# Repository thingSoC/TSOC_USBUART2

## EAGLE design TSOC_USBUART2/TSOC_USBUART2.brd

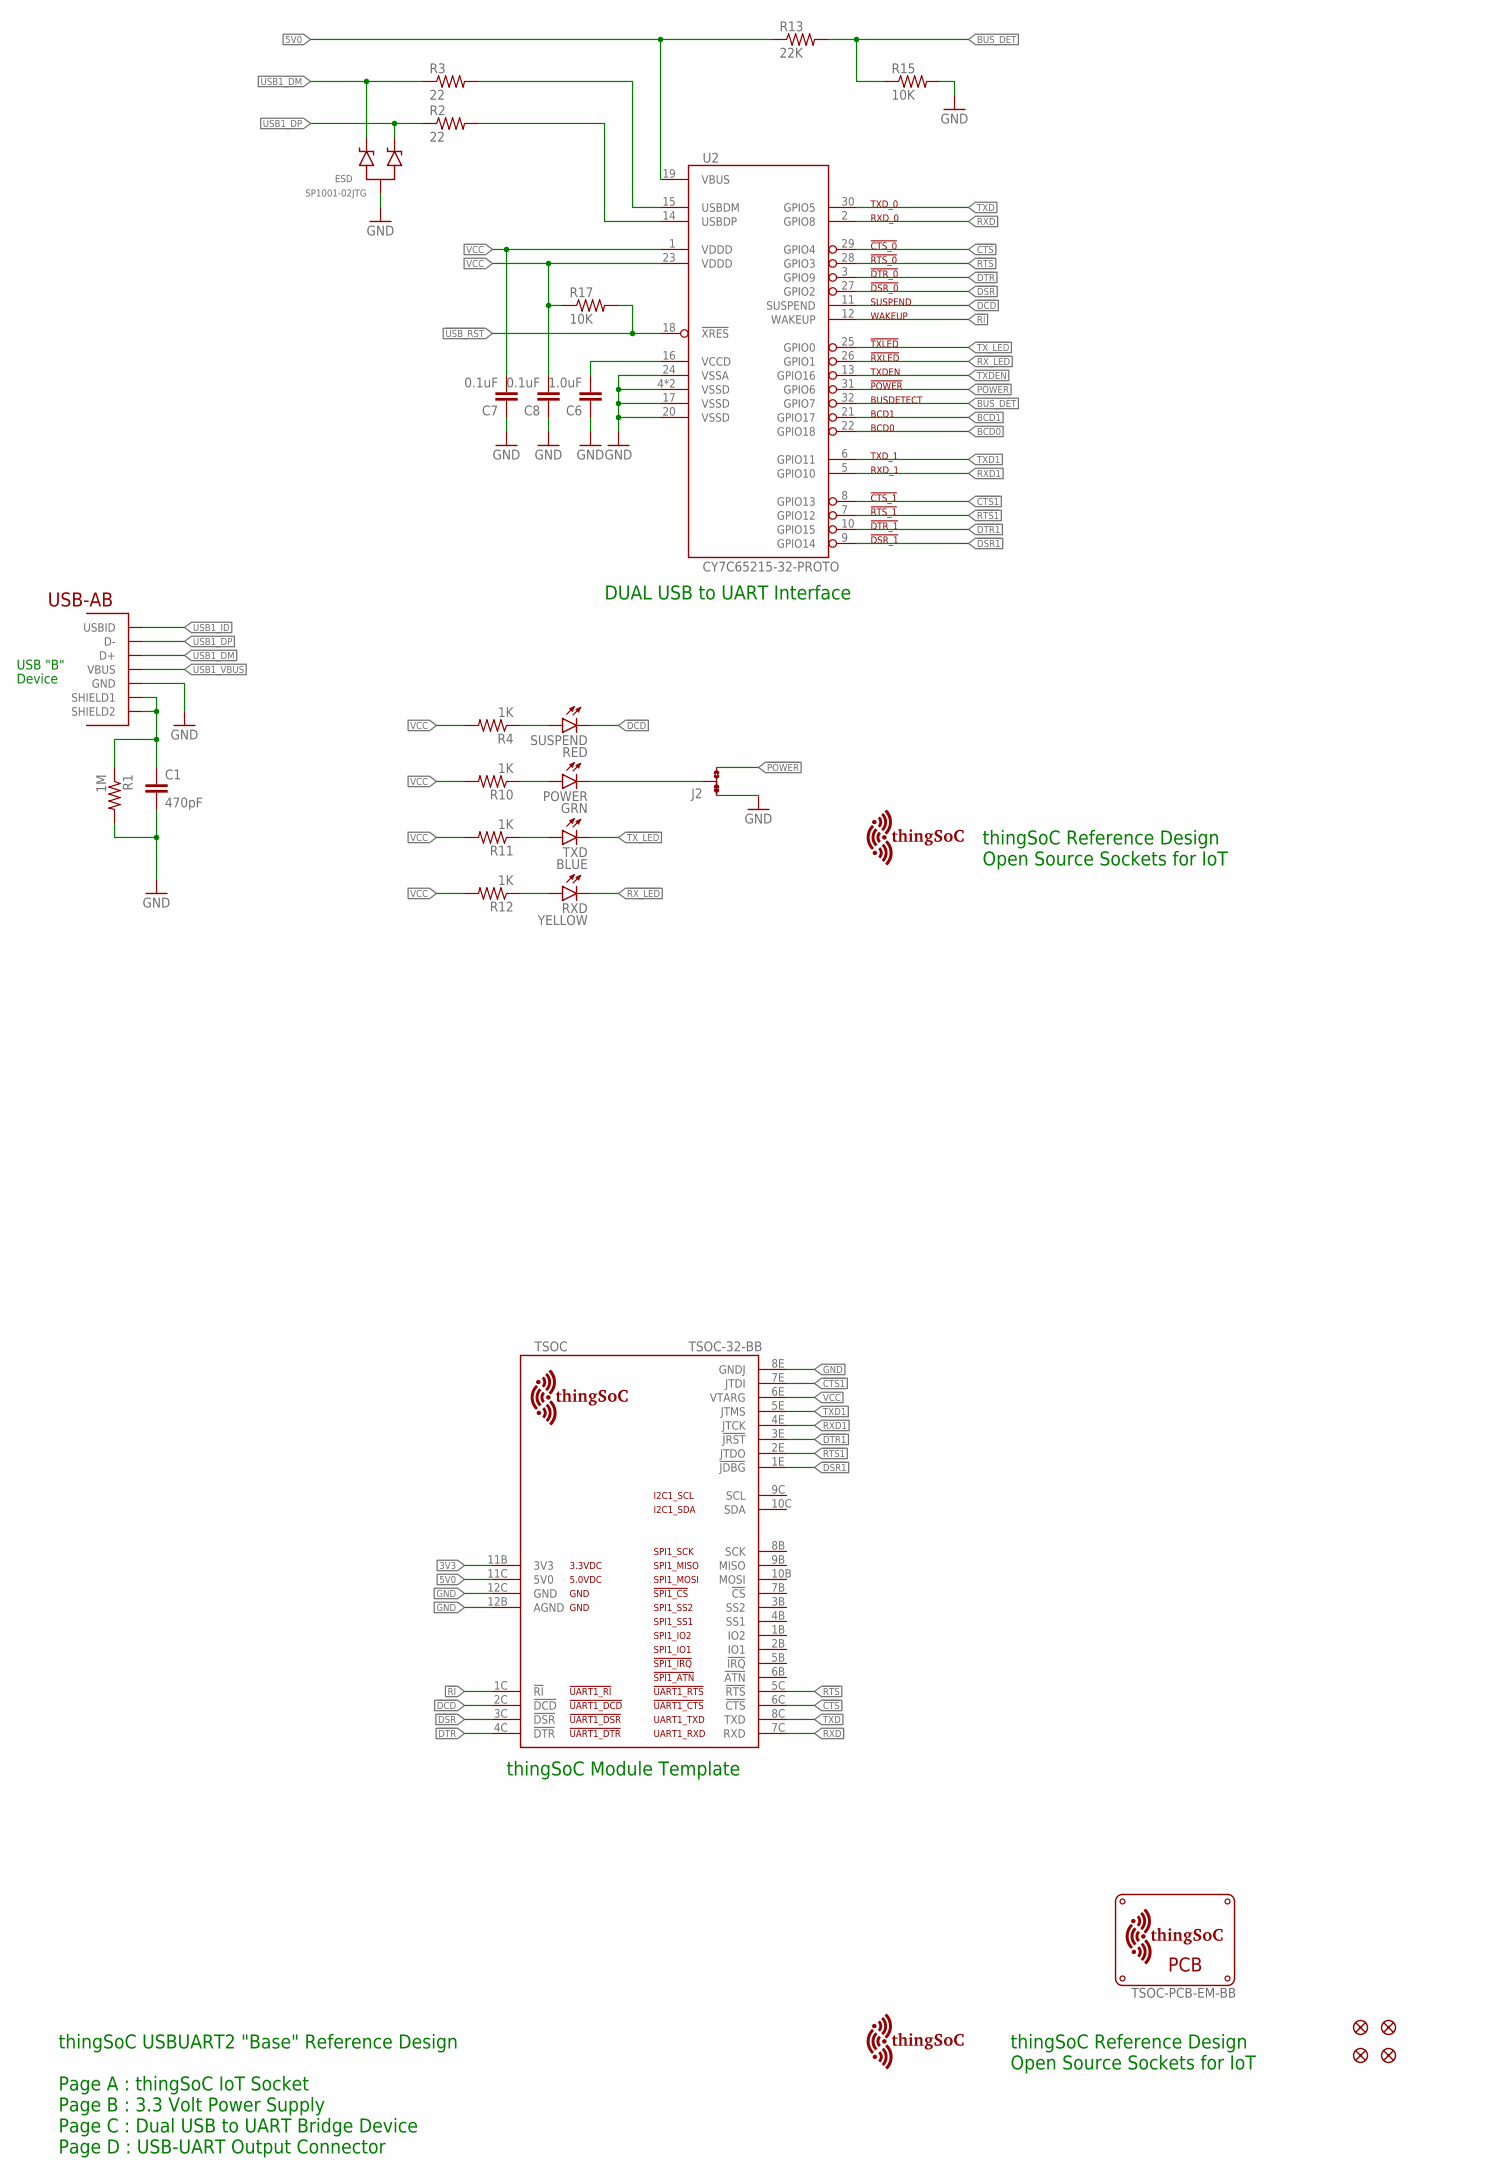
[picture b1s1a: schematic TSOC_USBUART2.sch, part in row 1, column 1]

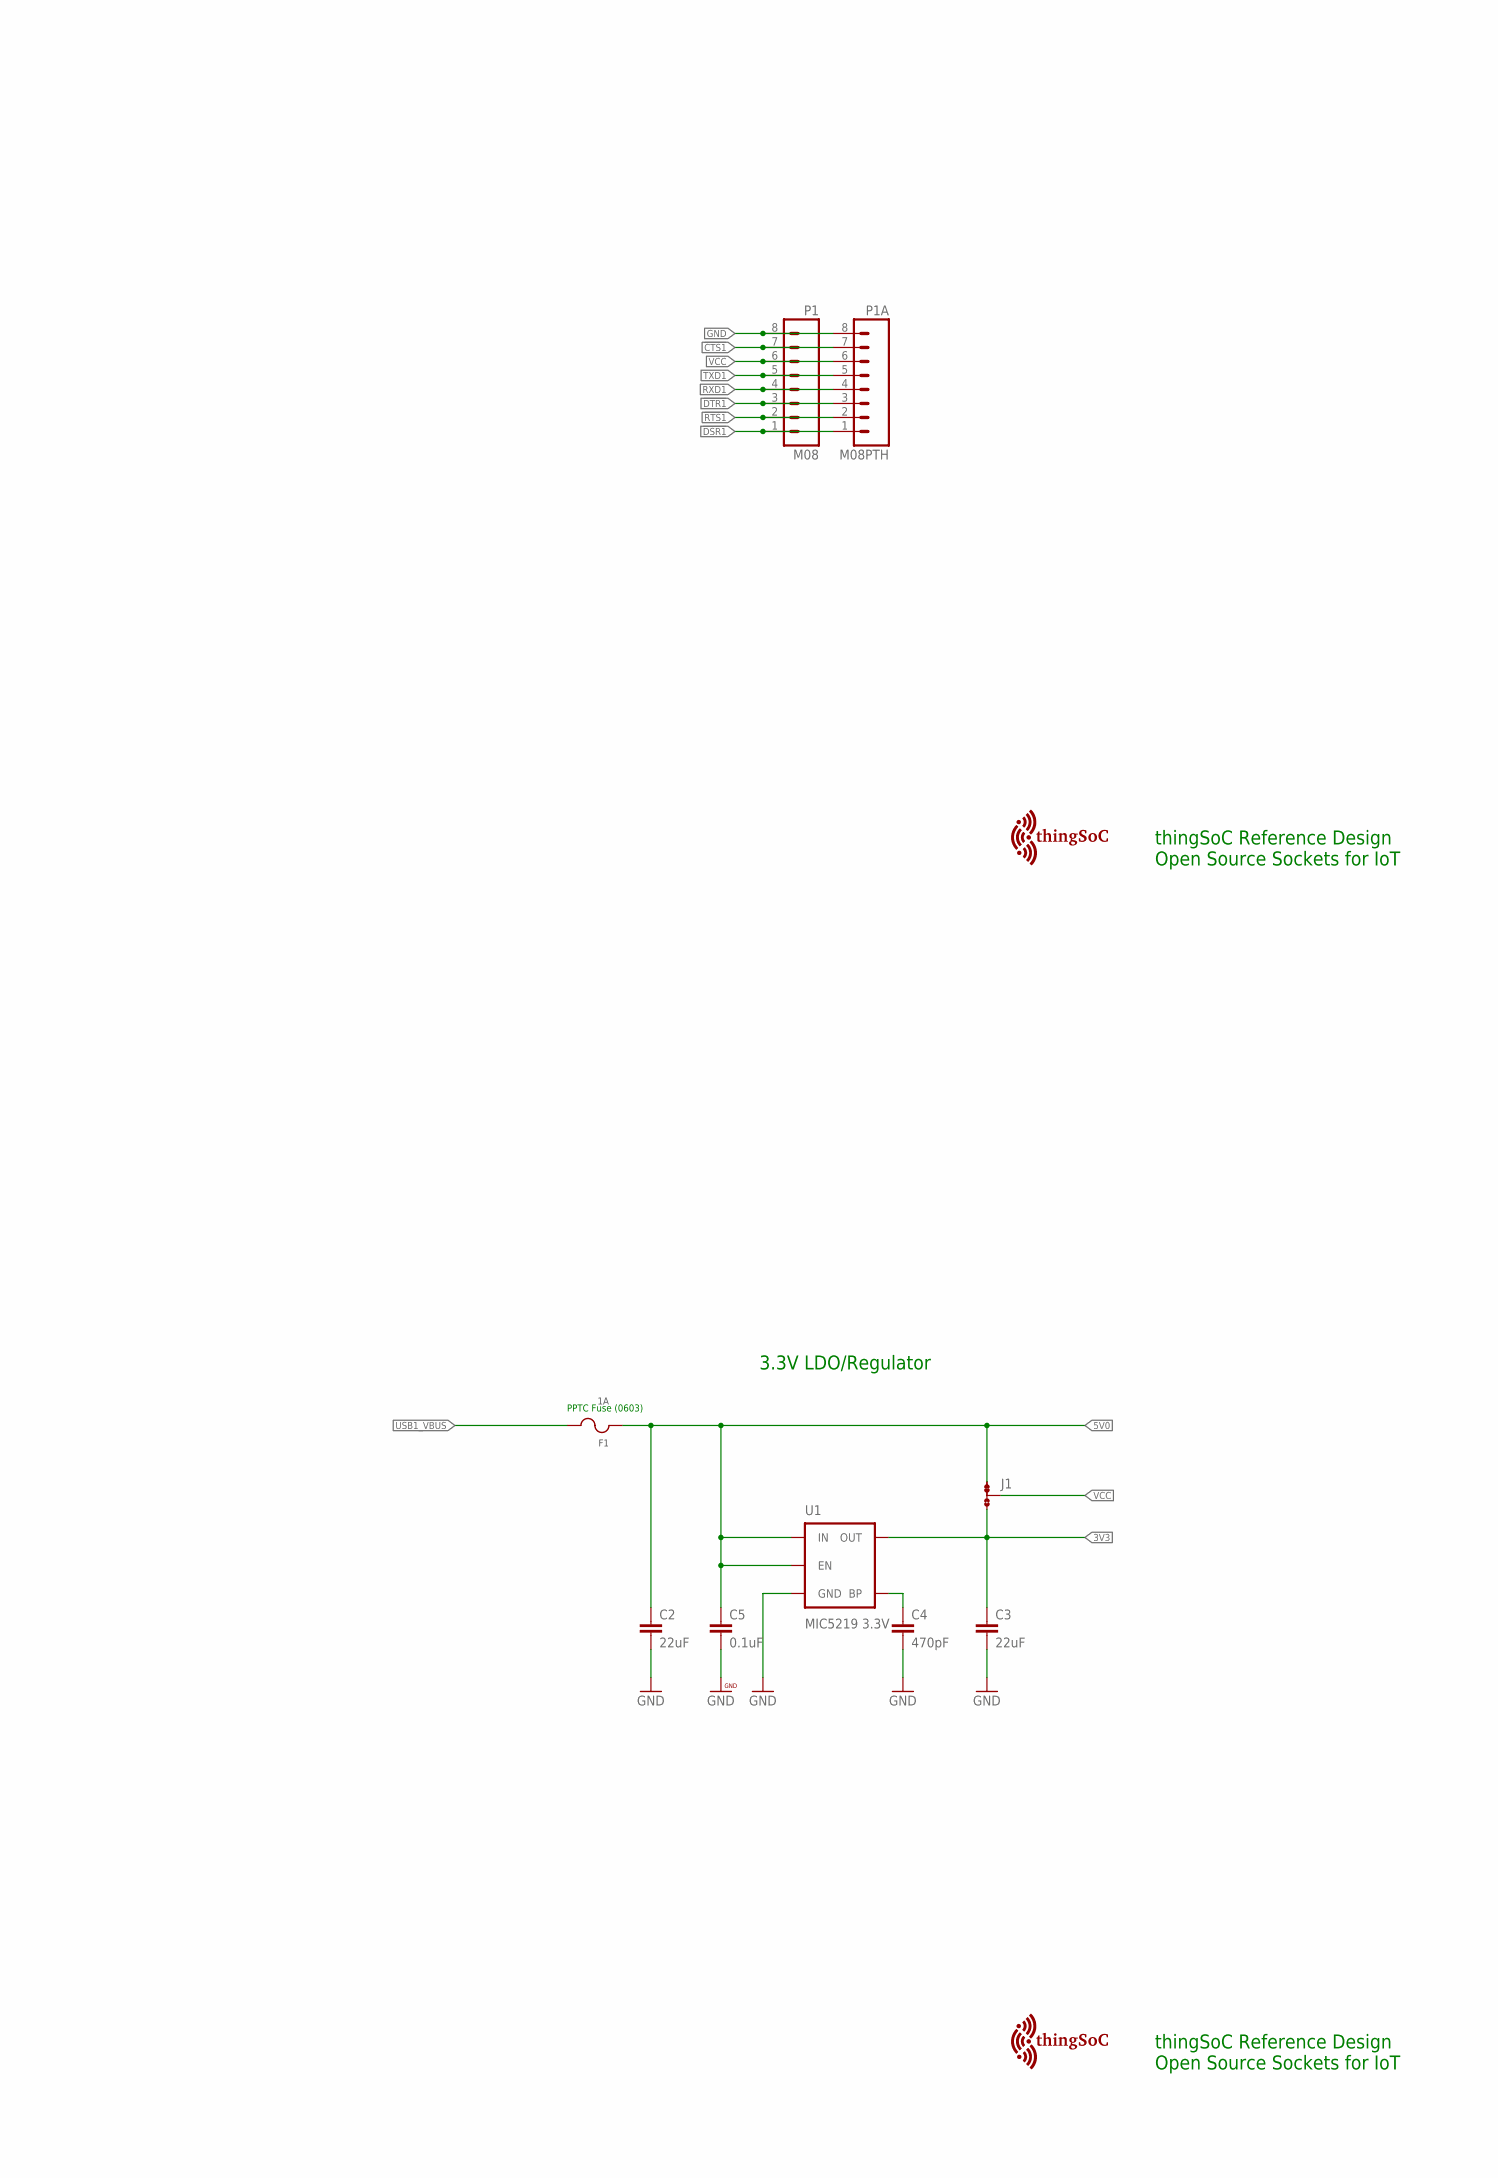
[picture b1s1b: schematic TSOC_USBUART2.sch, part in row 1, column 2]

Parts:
C1, C4: 470pF; EIA-0603
C2, C3: 22uF; EIA-1206
C5, C7, C8: 0.1uF; EIA-0603
C6: 1.0uF; EIA-0603
ESD: SP1001-02JTG; SC70-3
F1: 1A; EIA-0603
FID1, FID2, FID3, FID4: FIDUCIALUFIDUCIAL; MICRO-FIDUCIAL
J1, J2: JMP-3-1_2
P1: M08; 1X08-SMD-FEMALE
P1A: M08PTH; 1X08
POWER: GRN; LED-0603
R1: 1M; EIA-0603
R2, R3: 22; EIA-0603
R4, R10, R11, R12: 1K; EIA-0603
R13: 22K; EIA-0603
R15, R17: 10K; EIA-0603
RXD: YELLOW; LED-0603
SUSPEND: RED; LED-0603
TSOC: TSOC-32-BB; TSOC-BB-S32
TXD: BLUE; LED-0603
U1: MIC5219 3.3V; SOT23-5
U2: CY7C65215-32-PROTO; QFN32-PROTO
U$1: TSOC-PCB-EM-BB; TSOC-EM-BB
U$3: TSOC-LOGO-LRG
U$4, U$5, U$6: TSOC-LOGO; TSOC-LOGO-BLANK
USB: USB_AB; USB-AB-MICRO-SMD

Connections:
3V3: C3.1, J1.3, TSOC.11B (3V3), U1.5 (OUT)
5V0: C2.1, C5.1, F1.1, J1.1, R13.1, TSOC.11C (5V0), U1.1 (IN), U1.3 (EN), U2.19 (VBUS)
!CTS: TSOC.6C (!CTS), U2.29 (GPIO4)
!CTS1: P1.7, P1A.7, TSOC.7E (JTDI), U2.8 (GPIO13)
!DCD: SUSPEND.C, TSOC.2C (!DCD), U2.11 (SUSPEND)
!DSR: TSOC.3C (!DSR), U2.27 (GPIO2)
!DSR1: P1.1, P1A.1, TSOC.1E (!JDBG), U2.9 (GPIO14)
!DTR: TSOC.4C (!DTR), U2.3 (GPIO9)
!DTR1: P1.3, P1A.3, TSOC.3E (!JRST), U2.10 (GPIO15)
!POWER: J2.3, U2.31 (GPIO6)
!RI: TSOC.1C (!RI), U2.12 (WAKEUP)
!RTS: TSOC.5C (!RTS), U2.28 (GPIO3)
!RTS1: P1.2, P1A.2, TSOC.2E (JTDO), U2.7 (GPIO12)
!RX_LED: RXD.C, U2.26 (GPIO1)
!TX_LED: TXD.C, U2.25 (GPIO0)
!USB_RST: R17.2, U2.18 (!XRES)
BCD0: U2.22 (GPIO18)
BCD1: U2.21 (GPIO17)
BLU: R11.1, TXD.A
BUS_DET: R13.2, R15.1, U2.32 (GPIO7)
BYPASS1: C4.1, U1.4 (BP)
GND: C1.2, C2.2, C3.2, C4.2, C5.2, C6.1, C7.1, C8.1, ESD.3 (A), J2.1, P1.8, P1A.8, R1.2, R15.2, TSOC.8E (GNDJ), TSOC.12B (AGND), TSOC.12C (GND), U1.2 (GND), U2.4 (VSSD), U2.17 (VSSD), U2.20 (VSSD), U2.24 (VSSA), U2.EXP (VSSD), USB.GND
GRN: POWER.A, R10.1
PWR: J2.2, POWER.C
RED: R4.1, SUSPEND.A
RXD: TSOC.7C (RXD), U2.2 (GPIO8)
RXD1: P1.4, P1A.4, TSOC.4E (JTCK), U2.5 (GPIO10)
TXD: TSOC.8C (TXD), U2.30 (GPIO5)
TXD1: P1.5, P1A.5, TSOC.5E (JTMS), U2.6 (GPIO11)
TXDEN: U2.13 (GPIO16)
USB1_ID: USB.ID (USBID)
USB1_M: R3.2, U2.15 (USBDM)
USB1_P: R2.2, U2.14 (USBDP)
USB1_SHIELD: C1.1, R1.1, USB.SHIELD1, USB.SHIELD2
USB1_VBUS: F1.2, USB.VBUS
VCC: C7.2, C8.2, J1.2, P1.6, P1A.6, R4.2, R10.2, R11.2, R12.2, R17.1, TSOC.6E (VTARG), U2.1 (VDDD), U2.23 (VDDD)
VCCD1: C6.2, U2.16 (VCCD)
YEL: R12.1, RXD.A

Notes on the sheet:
thingSoC Reference Design Open Source Sockets for IoT
USB "B"
Device
thingSoC USBUART2 "Base" Reference Design Page A : thingSoC IoT Socket Page B : 3.3 Volt Power Supply Page C : Dual USB to UART Bridge Device Page D : USB-UART Output Connector
DUAL USB to UART Interface
thingSoC Module Template
3.3V LDO/Regulator
PPTC Fuse (0603)

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
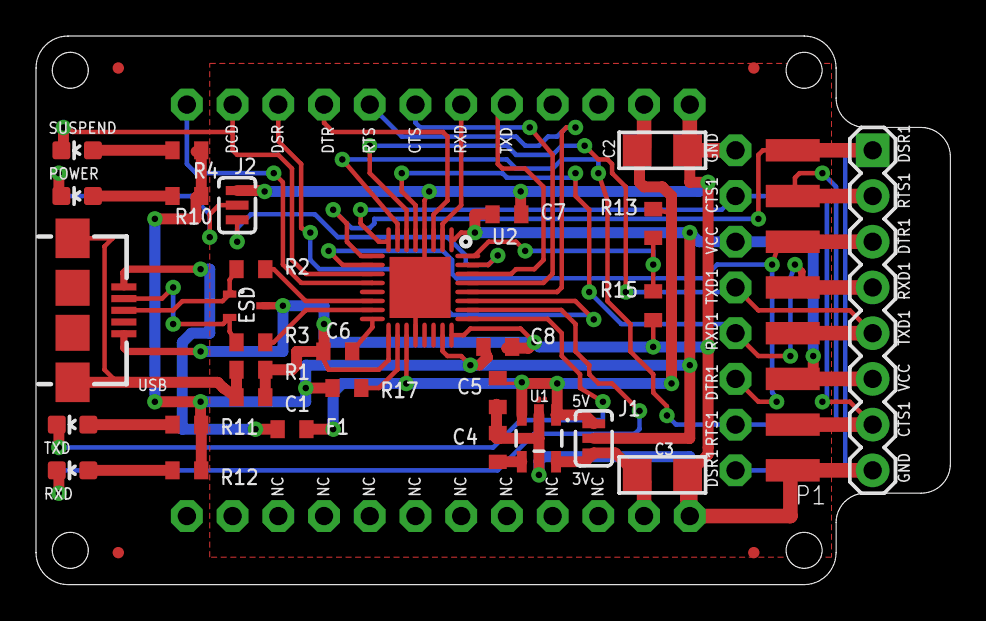
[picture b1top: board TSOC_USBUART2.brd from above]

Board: 2 copper layers, 50.8 x 30.5 mm, 41 parts (1 on the bottom side), 36 nets.

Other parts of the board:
U$7: TSOC-PCB-PLUSCUT; TSOC-BB-BRD-PLUS-CUT

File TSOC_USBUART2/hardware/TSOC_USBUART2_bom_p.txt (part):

Partlist exported from /home/moxon/github/TSOC-USBUART2/TSOC-USBUART2/TSOC_USBUART2.sch at 4/9/16 11:56 AM

Part    Value              Device             Package          Description                                                                                                                                                                               
C1      470pF              CAP-0603           EIA-0603         Ceramic Capacitor SMD                                                                                                                                                                     
C2      22uF               CAP-1206           EIA-1206         Ceramic Capacitor SMD                                                                                                                                                                     
C3      22uF               CAP-1206           EIA-1206         Ceramic Capacitor SMD                                                                                                                                                                     
C4      470pF              CAP-0603           EIA-0603         Ceramic Capacitor SMD                                                                                                                                                                     
C5      0.1uF              CAP-0603           EIA-0603         Ceramic Capacitor SMD                                                                                                                                                                     
C6      1.0uF              CAP-0603           EIA-0603         Ceramic Capacitor SMD                                                                                                                                                                     
C7      0.1uF              CAP-0603           EIA-0603         Ceramic Capacitor SMD                                                                                                                                                                     
C8      0.1uF              CAP-0603           EIA-0603         Ceramic Capacitor SMD                                                                                                                                                                     
ESD     SP1001-02JTG       SP1001-02JTG       SC70-3           Littelfuse SP1001-02JTG 
F1      1A                 FUSE               EIA-0603         Resettable PPTC Fuse - 0603 Footptint                                                                                                                                                                                                                                                                                                                 
J1      JMP-3-1_2          JMP-3-1_2          JMP-3-1_2        Three Terminal Jumper - 1 & 2 Connected                                                                                                                                                   
J2      JMP-3-1_2          JMP-3-1_2          JMP-3-1_2        Three Terminal Jumper - 1 & 2 Connected                                                                                                                                                   
P1      M08                M08                1X08-SMD-FEMALE                                                                                                                                                                                            
P1A     M08PTH             M08PTH             1X08                                                                                                                                                                                                       
POWER   GRN                LED0603            LED-0603         LEDs                                                                                                                                                                                      
R1      1M                 RESISTOR-0603      EIA-0603                                                                                                                                                                                                   
R2      22                 RESISTOR-0603      EIA-0603                                                                                                                                                                                                   
R3      22                 RESISTOR-0603      EIA-0603                                                                                                                                                                                                   
R4      1K                 RESISTOR-0603      EIA-0603                                                                                                                                                                                                   
R10     1K                 RESISTOR-0603      EIA-0603                                                                                                                                                                                                   
R11     1K                 RESISTOR-0603      EIA-0603                                                                                                                                                                                                   
R12     1K                 RESISTOR-0603      EIA-0603                                                                                                                                                                                                   
R13     22K                RESISTOR-0603      EIA-0603                                                                                                                                                                                                   
R15     10K                RESISTOR-0603      EIA-0603                                                                                                                                                                                                   
R17     10K                RESISTOR-0603      EIA-0603                                                                                                                                                                                                   
RXD     YELLOW             LED0603            LED-0603         LEDs                                                                                                                                                                                      
SUSPEND RED                LED0603            LED-0603         LEDs                                                                                                                                                                                                                                                                                                                                             
TXD     BLUE               LED0603            LED-0603         LEDs                                                                                                                                                                                      
U1      MIC5219 3.3V       V_REG_MIC52193.3V  SOT23-5          V_REG MIC5219                                                                                                                                                                             
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

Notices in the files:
parts and their libraries:
thingSoC: License : http://creativecommons.org/licenses/by-sa/4.0
(Creative Commons 4.0)
PatternAgents-Cypress: License : http://creativecommons.org/licenses/by-sa/3.0
(Creative Commons 3.0)
